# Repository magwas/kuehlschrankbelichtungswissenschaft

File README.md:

# Kühlschrankbelichtungswissenschaft

Kühlschrankbelichtungswissenschaft means "fridge lighting science".
It is an open hardware, open source steampunk control unit for agriculture projects, with two set of the following features:

- controlled 220V mains plug for a lamp
- humidity sensor as a 3.5mm audio socket
- CO2 sensor
- two temperature sensors
- controlled 12V barrel outlets for ventillation, cooling, nutrient and heating

The CO2 and temperature sensors are connected using RJ11 connectors with the following pinout:

1. GND (green)
2. 3V3 (green-white)
3. SDA (brown)
4. SCL (brown-white)
5. 5V (red)
6. OneWire (red-white)

The ground of the connectors for RJ11 is controlled, as the CO2 sensor used have a fix I2C address.

The circuit design is in the conteroller directory.

The schematics layout looks as it is to make it easier to implement it as a freeform circuit.
This is the reason there is no PCB design. Of course you are welcome to build it on a PCB.
A two-sided PCB should be adequate for the job, there is nothing placement-critical there.

I did not put the USB-c cable between the board and the connector on the chassis on the circuit design,
simply because the symbol I use does not contain it.

## SOFTWARE INSTALLATION

The software uses ESP IDF, and the msglib library.
Install ESP IDF as documented at https://docs.espressif.com/projects/esp-idf/en/latest/esp32/get-started/
Clone msglib to a convenient place, like
```
mkdir ~/build
cd ~/build
git clone https://github.com/magwas/msglib
```

to build, flash and monitor the software, plug in the board to the USB, export MESSAGING_LIB with the location where you cloned it, activate ESP IDF, and run idf.py build, something like

```
export MESSAGING_LIB=$HOME/build/msglib
. ~/.espressif/tools/activate_idf_v5.5.2.sh ~/idf-esp-activate
idf.py -p /dev/ttyACM0 build flash monitor
```

## HARDWARE FABRICATION

The mechanical design is in the FreeCad model box.CFStd. I have a Snapmaker 2, so the CNC jobs use the marlin preprocessor.

The fixjobs.sh script

- fixes the output of the preprocessor (marlin emits M3 S100, snapmaker understands M3 P100, and the comments are in different form)
- removes all Z movement from the laser engraving jobs, replacing some of the to gcode turning the laser off and on again.

IMPORTANT: the engraving job fix translates movement to Z=26 (G0 Z26.000) to turning the laser off, and Z=21 (G0 Z21.000) to turning it on.
Make sure that the heights and depths of the engraving job correspont to these if you modify it.

postprocess all of the CNC jobs. The "Stock Prepare" job is for preparation of the stock on my own machine, you might of course choose other ways to fix your stock.
run fixjobs.sh or something equivalent for your setup.
the file cnc-workflow contains the instructions to do the milling and engraving. It contains the sizes of the stocks. I recommend to use some hardwood. I used white acacia, as I love that wood. You will need a 128x86 and 246x86 mm sheet of 4mm tempered glass.
Populate the dashboard with components. I try to recall here what I was using. Be aware that they are mostly cheap noname parts. Which means you can probably buy ones with similar sizes.

- For the mains plugs, I cannibalized some LEGRAND SUNO plugs, by removing everything above the bottom plastic and metal parts, and trimming down the plastic parts, keeping the tabs which open the electrodes for the assembly.
- The main switch is a 22x30 standard switch.
- The 12V barrel connectors I obtained are for 12mm diameter fine thread. I did not want to buy a tap for that, instead I made the holes the size such that they fit snuggly.
 - Vents are standard PC ventillators
 - The cooling pumps are 12V pumps I bought on eBay. The cooling is a mix of 6mm outer diameter copper and 6mm inner diameter silicone tubes.
 - The nutrient dosage pumps are just like the cooling pumps.
 - I actually do not yet have heating. I plan to coil up some heating wires for that purpose on some ceramics.
- The USB-C connector is a noname one which fits into the 3.5x10mm hole and its length is 15mm. I could not find a datasheet for a similar one.
- The connectors for the humidity sensors are standard 3.5mm audio jacks. They are actually the tye of swinging connector wher the round connector part is fixed to the anti-fracture housing with a thread. I use just the inner part. The humidity sensors are just steel rods (~10cm sut from bicycle spokes) placed 1 cm apart.
- The design now have just a simple hole for the wifi antenna, as I am currently waiting for the board wersion which comes with a connector for it.
- The RJ11 connectors are the plain usual 90 degree ones.

All other components (and most of the aboveones ) are in the BOM of the circuit.

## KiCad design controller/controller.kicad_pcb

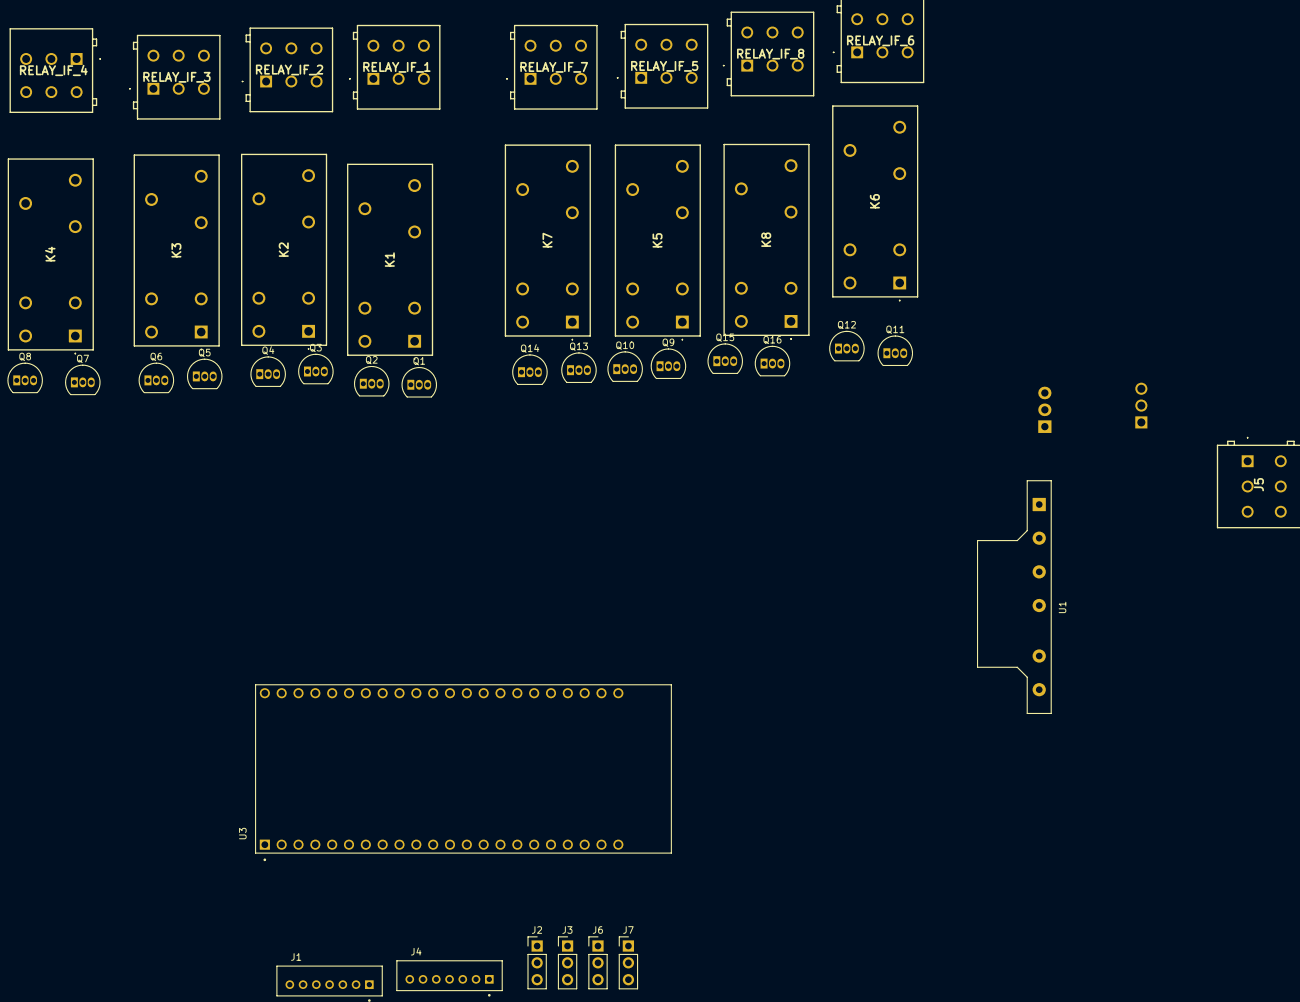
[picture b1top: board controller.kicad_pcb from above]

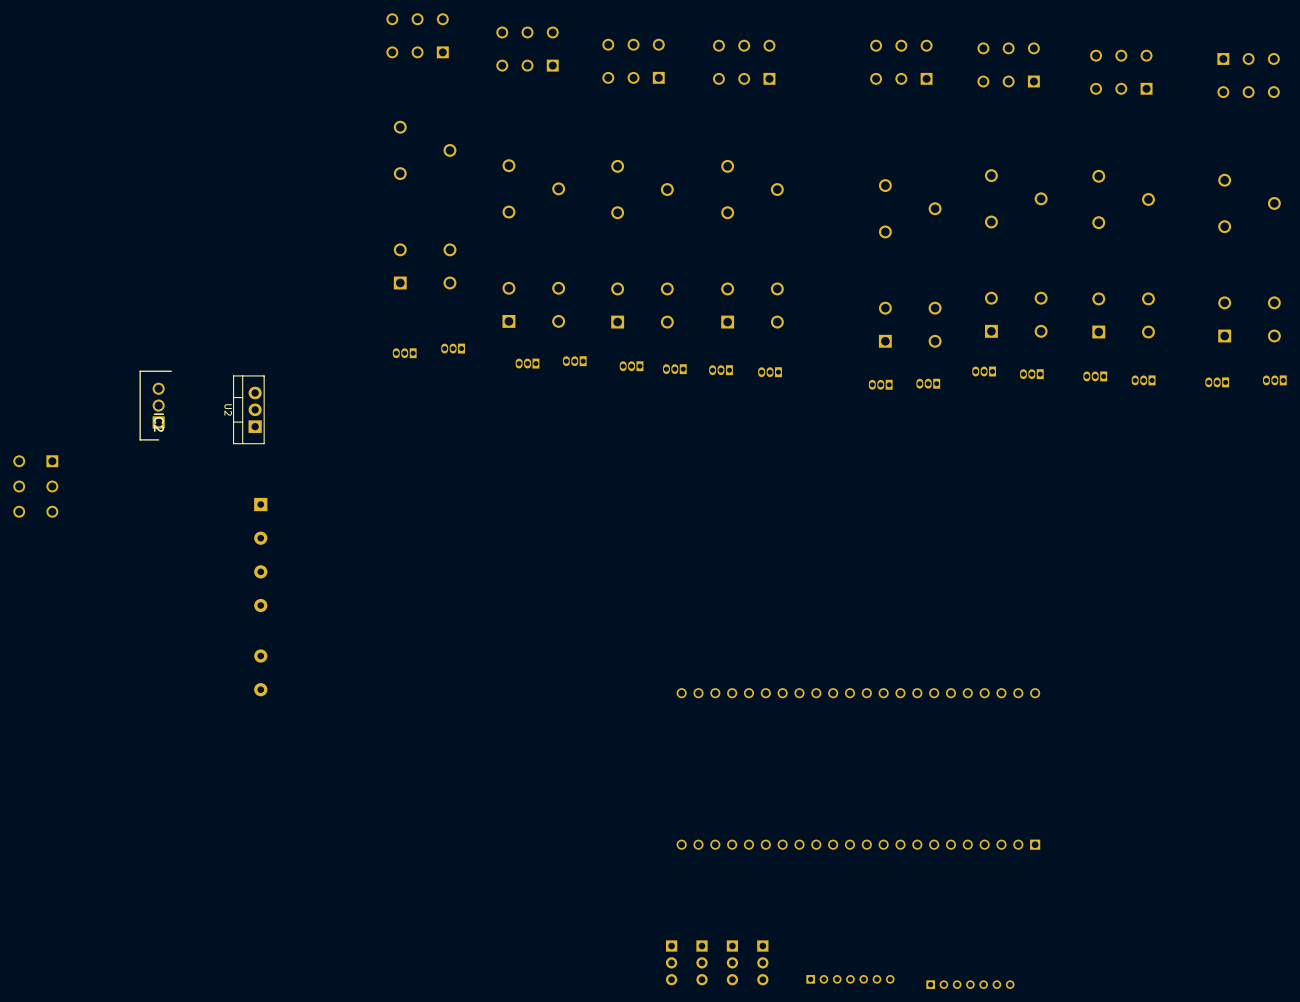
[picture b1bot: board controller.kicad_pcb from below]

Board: 2 copper layers, 43 parts (2 on the bottom side), 67 nets, no tracks yet.

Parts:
IC2: UA78M33CKCS; TO254P470X1016X1965-3P
J1, J4: B7B-PH-K-S; JST_B7B-PH-K-S
J2, J3, J6, J7: Conn_01x03_Pin; PinHeader_1x03_P2.54mm_Vertical
J5: Screw_Terminal_01x03; TBL00138103GY2GY
K1, K2, K3, K4, K5, K6, K7, K8: G2RK-1-DC5; G2RK1DC5
Q1, Q2, Q3, Q4, Q5, Q6, Q7, Q8, Q9, Q10, Q11, Q12, Q13, Q14, Q15, Q16: BS170; TO-92_Inline
RELAY_IF_1, RELAY_IF_2, RELAY_IF_3, RELAY_IF_4, RELAY_IF_5, RELAY_IF_6, RELAY_IF_7, RELAY_IF_8: ST; TBL00138103GY2GY
U1: PBO-3E-12; Converter_ACDC_CUI_PBO-3-Sxx_THT_Vertical
U2: LM7805_TO220; TO-220-3_Vertical
U3: ESP32-S3-DEVKITC-1-N8R8

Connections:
/CO0_RX: J4.6, U3.J1_11 (GPIO18)
/CO0_TX: J4.5, U3.J1_10 (GPIO17)
/CO1_RX: J1.6, U3.J1_6 (GPIO6)
/CO1_TX: J1.5, U3.J1_5 (GPIO5)
/OneVire: J2.2, J3.2, J6.2, J7.2, U3.J1_4 (GPIO4)
GND: IC2.2 (COMMON), J1.3, J2.3, J3.3, J4.3, J6.3, J7.3, K1.1 (COIL_S-), K1.2 (COIL_R-), K2.1 (COIL_S-), K2.2 (COIL_R-), K3.1 (COIL_S-), K3.2 (COIL_R-), K4.1 (COIL_S-), K4.2 (COIL_R-), K5.1 (COIL_S-), K5.2 (COIL_R-), K6.1 (COIL_S-), K6.2 (COIL_R-), K7.1 (COIL_S-), K7.2 (COIL_R-), K8.1 (COIL_S-), K8.2 (COIL_R-), U1.10 (-Vo), U2.2 (GND), U3.J1_22 (GND3), U3.J3_1 (GND), U3.J3_21 (GND1), U3.J3_22 (GND2)
unnamed: K3.7 (COIL_S+), Q5.3 (S)
unnamed: K3.6 (COIL_R+), Q6.3 (S)
unnamed: IC2.1 (INPUT), U1.12 (+Vo), U2.1 (VI)
unnamed: J5.2, U1.1 (AC(N))
unnamed: J5.3, U1.3 (AC(L))
unnamed: K1.6 (COIL_R+), Q2.3 (S)
unnamed: K1.7 (COIL_S+), Q1.3 (S)
unnamed: K1.5 (COM), RELAY_IF_1.1
unnamed: K1.3 (NC), RELAY_IF_1.3
unnamed: K1.4 (NO), RELAY_IF_1.2
unnamed: K2.6 (COIL_R+), Q4.3 (S)
unnamed: K2.7 (COIL_S+), Q3.3 (S)
unnamed: K2.5 (COM), RELAY_IF_2.1
unnamed: K2.3 (NC), RELAY_IF_2.3
unnamed: K2.4 (NO), RELAY_IF_2.2
unnamed: K3.5 (COM), RELAY_IF_3.1
unnamed: K3.3 (NC), RELAY_IF_3.3
unnamed: K3.4 (NO), RELAY_IF_3.2
unnamed: K4.6 (COIL_R+), Q8.3 (S)
unnamed: K4.7 (COIL_S+), Q7.3 (S)
unnamed: K4.5 (COM), RELAY_IF_4.1
unnamed: K4.3 (NC), RELAY_IF_4.3
unnamed: K4.4 (NO), RELAY_IF_4.2
unnamed: K5.6 (COIL_R+), Q10.3 (S)
unnamed: K5.7 (COIL_S+), Q9.3 (S)
unnamed: K5.5 (COM), RELAY_IF_5.1
unnamed: K5.3 (NC), RELAY_IF_5.3
unnamed: K5.4 (NO), RELAY_IF_5.2
unnamed: K6.6 (COIL_R+), Q12.3 (S)
unnamed: K6.7 (COIL_S+), Q11.3 (S)
unnamed: K6.5 (COM), RELAY_IF_6.1
unnamed: K6.3 (NC), RELAY_IF_6.3
unnamed: K6.4 (NO), RELAY_IF_6.2
unnamed: K7.6 (COIL_R+), Q14.3 (S)
unnamed: K7.7 (COIL_S+), Q13.3 (S)
unnamed: K7.5 (COM), RELAY_IF_7.1
unnamed: K7.3 (NC), RELAY_IF_7.3
unnamed: K7.4 (NO), RELAY_IF_7.2
unnamed: K8.6 (COIL_R+), Q16.3 (S)
unnamed: K8.7 (COIL_S+), Q15.3 (S)
unnamed: K8.5 (COM), RELAY_IF_8.1
unnamed: K8.3 (NC), RELAY_IF_8.3
unnamed: K8.4 (NO), RELAY_IF_8.2
RELAY_1_OFF: Q2.2 (G), U3.J1_12 (GPIO8)
RELAY_1_ON: Q1.2 (G), U3.J1_15 (GPIO9)
RELAY_2_OFF: Q4.2 (G), U3.J1_16 (GPIO10)
RELAY_2_ON: Q3.2 (G), U3.J1_17 (GPIO11)
RELAY_3_OFF: Q6.2 (G), U3.J1_18 (GPIO12)
RELAY_3_ON: Q5.2 (G), U3.J1_19 (GPIO13)
RELAY_4_OFF: Q8.2 (G), U3.J1_20 (GPIO14)
RELAY_4_ON: Q7.2 (G), U3.J1_8 (GPIO15)
RELAY_5_OFF: Q10.2 (G), U3.J3_17 (GPIO47)
RELAY_5_ON: Q9.2 (G), U3.J3_16 (GPIO48)
RELAY_6_OFF: Q12.2 (G), U3.J3_13 (GPIO35)
RELAY_6_ON: Q11.2 (G), U3.J3_12 (GPIO36)
RELAY_7_OFF: Q14.2 (G), U3.J3_11 (GPIO37)
RELAY_7_ON: Q13.2 (G), U3.J3_10 (GPIO38)
RELAY_8_OFF: Q16.2 (G), U3.J3_4 (GPIO1)
RELAY_8_ON: Q15.2 (G), U3.J3_5 (GPIO2)
VCC: J1.4, J4.4, Q1.1 (D), Q2.1 (D), Q3.1 (D), Q4.1 (D), Q5.1 (D), Q6.1 (D), Q7.1 (D), Q8.1 (D), Q9.1 (D), Q10.1 (D), Q11.1 (D), Q12.1 (D), Q13.1 (D), Q14.1 (D), Q15.1 (D), Q16.1 (D), U2.3 (VO), U3.J1_21 (5V0)
VDD: IC2.3 (OUTPUT), J2.1, J3.1, J6.1, J7.1

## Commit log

2025-11-08 initial checkin
2025-11-08 deleted unused schematic files
2025-11-10 made symbols and footprint relative to project
2025-11-15 schematics with 5050 leds ready
2025-11-16 fixup
2025-11-16 using single and dual top switch current driver circuits
2025-11-17 RTC added
2025-11-17 led pcb designed
2025-11-19 beginning of hardware
2025-11-19 fixup: housekeep.h
2025-11-19 changed measurement resistor in current driver
2025-11-20 NDBG504F3950B1F thermistor calibration data and temperature calculation
2025-11-20 dumped soil humidity sensor design to soilHumidity.cc
2025-12-08 MessageQueue is tested
2025-12-08 top switch, capacitor design doc
2025-12-09 message queue redesign
2025-12-09 lamp refactored
2025-12-10 NTC_thermistor refactored to class
2025-12-10 thermometer refactored to class
2025-12-10 Error log
2025-12-10 fix branch in version generation
2025-12-10 lamp related commands
2025-12-10 clock commands
2025-12-10 ErrorLog user interface
2025-12-10 better error messages
2025-12-15 compile errors, battery backup, restruct
    - compile errors on lack of #defines
    - clock battery backup configured
    - 1sec interrupt moved to clock, housekeep runs on message
    - console messages instead of printfs
2025-12-19 moved device drivers and services to library
2025-12-19 relayed lamp project started
2025-12-20 better Makefile, works on hardware
2025-12-30 moved som libs to header-only
2026-01-17 box design
2026-01-17 messagequeue and thermometer fixes
2026-01-17 engraving of all labels
2026-01-25 new version of box
2026-01-25 jobs for all box parts, job fixer update
2026-01-30 CNC workflow, job fixes
2026-01-30 through jobs go through
2026-01-30 jack holes
2026-01-30 stock prepare, same origo
2026-01-30 4.2 clearance holes for stock
2026-01-30 tags in profiles
2026-01-30 purging unused symbols and footprints
2026-01-30 deleted all schematics, they are outdated and never realized
2026-02-02 schematics
2026-02-02 README, software
2026-02-02 sensors
2026-02-02 wider space for glasses and mains plug rods, humidity sensor body
2026-02-18 fixed bottom part and CAM jobs
2026-02-18 turned wifi back on
2026-02-18 Tags fixed on bottom plate
2026-02-18 More beefy tags on all perimeter profiles
2026-02-26 updated relays and 250V part with actual circuit
2026-02-26 glass slots redesigned to be 5mm wide
    They are recentered to be 2mm from both sides.
    Hopefully this will be wide enough for my 4mm+painting test glass
    closes: #1
2026-03-08 CAM job checking and preparation
    There are check for the cam operations to make sure no regression happens.
    All the following is checked and fixed in the model:
    - dressup tags size
    - output file name
    - profile final depth
    - pocket pattern and step over ( closes: #2)
2026-03-08 fix RJ11 profile, fixup script confusion
    Changed the last RJ11 operation to profile the whole hole in one run. fixes: #3
    there was a naming confusion and save_cam_operations macro was missing. fixed than up
2026-03-08 RJ11 pocket extension
    added extension to RJ11 pockets. closes: #4
2026-03-11 screw head pockets
    closes: #6
2026-03-11 Antenna hole correct diameter
    closes: #8
2026-03-11 Engraving of console label fixed
    fixes: #7
